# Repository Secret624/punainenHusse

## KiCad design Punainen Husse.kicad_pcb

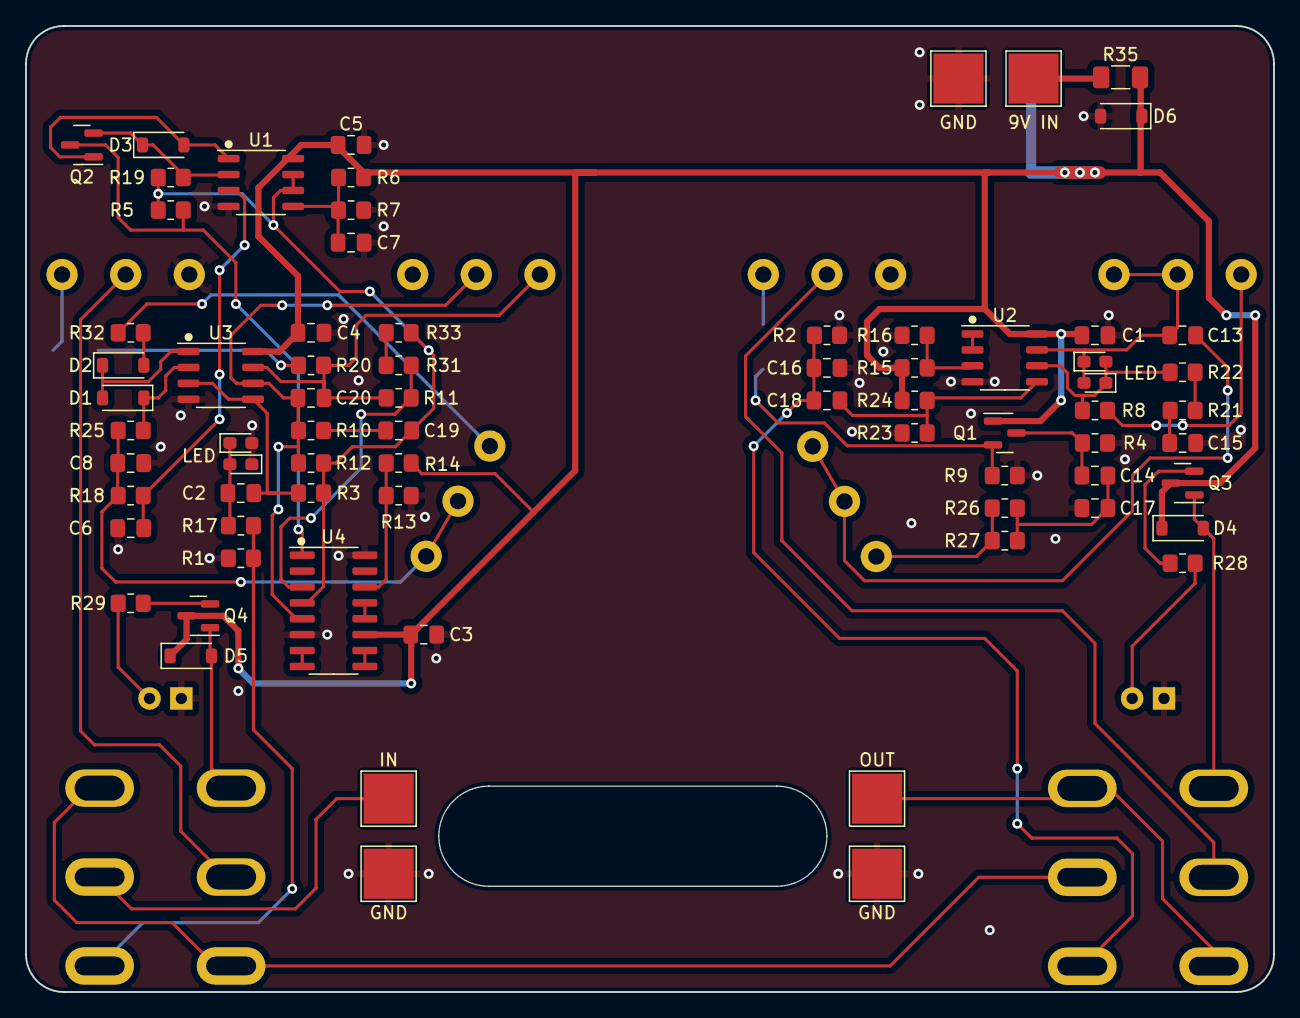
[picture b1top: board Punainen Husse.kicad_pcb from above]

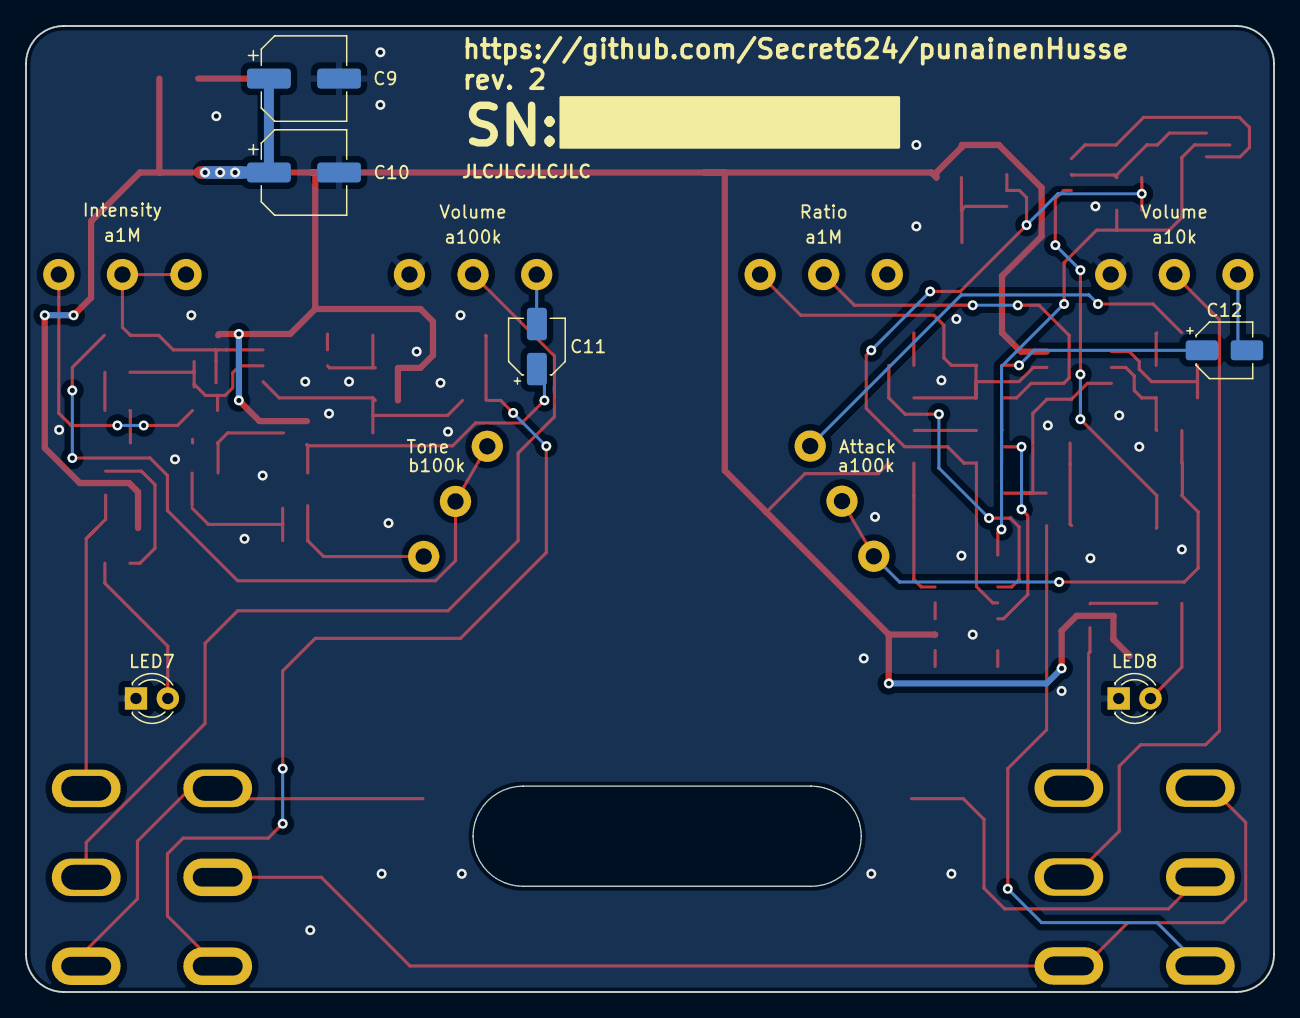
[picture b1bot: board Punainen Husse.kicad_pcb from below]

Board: 2 copper layers, 99.7 x 77.1 mm, 87 parts (14 on the bottom side), 54 nets.

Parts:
C1, C2, C3, C4, C5: 10nF; C_0805_2012Metric_Pad1.18x1.45mm_HandSolder
C6, C7, C8: 1uF; C_0805_2012Metric_Pad1.18x1.45mm_HandSolder
C9, C10: 100uF; CP_Elec_6.3x5.4
C11, C12: 10uF; CP_Elec_4x5.4
C13, C14: 100nF; C_0805_2012Metric_Pad1.18x1.45mm_HandSolder
C15: 220nF; C_0805_2012Metric_Pad1.18x1.45mm_HandSolder
C16: 1nF; C_0805_2012Metric_Pad1.18x1.45mm_HandSolder
C17: 3.3nF; C_0805_2012Metric_Pad1.18x1.45mm_HandSolder
C18: 47nF; C_0805_2012Metric_Pad1.18x1.45mm_HandSolder
C19: 4.7nF; C_0805_2012Metric_Pad1.18x1.45mm_HandSolder
C20: 100pF; C_0805_2012Metric_Pad1.18x1.45mm_HandSolder
D1, D2, D3, D4, D5: 1N4148W; D_SOD-123
D6: 1N4001; D_SOD-123
LED1, LED2, LED3, LED4: LED_Small; LED_0603_1608Metric_Pad1.05x0.95mm_HandSolder
LED7, LED8: LED_Small; LED_D3.0mm
Q1: MMBF4393LT1G; SOT-23
Q2: BC807; SOT-23
Q3, Q4: MMBF170; SOT-23
R1, R2, R3, R4, R5, R6, R7: 1M; R_0805_2012Metric_Pad1.20x1.40mm_HandSolder
R8, R9, R10, R11, R12, R13, R14, R15, R16: 10k; R_0805_2012Metric_Pad1.20x1.40mm_HandSolder
R17, R18, R19, R20, R21, R22: 1k; R_0805_2012Metric_Pad1.20x1.40mm_HandSolder
R23, R24, R25: 470k; R_0805_2012Metric_Pad1.20x1.40mm_HandSolder
R26, R27, R28, R29: 4.7k; R_0805_2012Metric_Pad1.20x1.40mm_HandSolder
R31, R32, R33: 100Ω; R_0805_2012Metric_Pad1.20x1.40mm_HandSolder
R35: 39Ω; R_1206_3216Metric_Pad1.30x1.75mm_HandSolder
Rv1, Rv5: a1M; UT right angle long pin
Rv2: b100k; UT right angle long pin
Rv3, Rv4: a100k; UT right angle long pin
Rv6: a10k; UT right angle long pin
SW1, SW2: SW_DPDT_x2; Ural dpdt
TP1: OUT; TestPoint_Pad_4.0x4.0mm
TP2: IN; TestPoint_Pad_4.0x4.0mm
TP3, TP4, TP11: GND; TestPoint_Pad_4.0x4.0mm
TP12: 9V IN; TestPoint_Pad_4.0x4.0mm
U1, U2, U3: TL072; SO-8_3.9x4.9mm_P1.27mm
U4: LM13700; SOP-16_3.9x9.9mm_P1.27mm

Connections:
9V in: R35.1, TP12.1
+5V: C19.2, R3.1, R5.1, R12.1, R19.1, R33.2, U1.6 (-), U1.7, U4.4 (-)
+9V: C1.1, C3.1, C4.1, C5.1, C9.1, C10.1, D4.1 (K), D5.1 (K), D6.1 (K), Q1.1 (D), Q3.3 (D), Q4.3 (D), R6.1, R14.1, R15.1, R24.1, R35.2, U1.8 (V+), U2.8 (V+), U3.8 (V+), U4.11 (V+)
FS_engi: D5.2 (A), Q4.1 (G), SW2.4 (A)
FS_red: D4.2 (A), Q3.1 (G), SW1.4 (A)
GND: C1.2, C3.2, C4.2, C5.2, C6.2, C7.1, C8.2, C9.2, C10.2, C15.2, C16.2, C17.2, D6.2 (A), LED3.1 (K), LED4.2 (A), LED7.1 (K), LED8.1 (K), R1.2, R2.2, R4.2, R7.2, R9.2, R13.2, R16.2, R23.2, Rv3.1, Rv6.1, TP3.1, TP4.1, TP11.1, U1.4 (V-), U2.4 (V-), U3.4 (V-), U4.6 (V-), U4.16
IN_engi: SW2.2 (B), TP2.1
IN_engi_pcb: R1.1, R17.1, SW2.1 (A)
IN_red: SW1.2 (B), SW2.3 (C), SW2.6 (C)
IN_red_pcb: C16.1, C18.1, R2.1, SW1.1 (A)
unnamed: C8.1, R18.1, R25.1, Rv4.2, Rv4.3
unnamed: C11.2, Rv3.3
unnamed: C12.1, R20.2
unnamed: C12.2, Rv6.3
unnamed: C13.1, Rv2.2, Rv2.3
unnamed: C14.2, C17.1, R26.1, R27.1
unnamed: C15.1, R21.2
unnamed: C19.1, R10.1
unnamed: C20.1, R11.2, R20.1, Rv5.1, U3.7
unnamed: D1.2 (A), D2.1 (K), U3.1
unnamed: D1.1 (K), R25.2, U3.2 (-)
unnamed: D2.2 (A), R32.1
unnamed: D3.2 (A), Q2.1 (B), U1.1
unnamed: D3.1 (K), Q2.2 (E), R19.2, U1.2 (-)
unnamed: C13.2, LED1.2 (A), LED2.1 (K), Rv1.2, Rv1.3, U2.7
unnamed: LED1.1 (K), LED2.2 (A), R8.2, R22.2, U2.6 (-)
unnamed: C2.2, LED3.2 (A), LED4.1 (K), R17.2
unnamed: LED7.2 (A), R28.2
unnamed: LED8.2 (A), R29.2
unnamed: C14.1, Q1.3 (G), R4.1
unnamed: C11.1, Q1.2 (S), R9.1
unnamed: Q2.3 (C), R5.2, U4.1
unnamed: Q3.2 (S), R28.1
unnamed: Q4.2 (S), R29.1
unnamed: R8.1, Rv1.1
unnamed: R21.1, R22.1
unnamed: R26.2, R27.2, Rv2.1
unnamed: R31.2, R33.1
unnamed: R32.2, Rv4.1
unnamed: C6.1, R18.2, U1.3 (+)
unnamed: C7.2, R6.2, R7.1, U1.5 (+)
unnamed: R15.2, R16.1, U2.3 (+)
unnamed: U2.1, U2.2 (-)
unnamed: C18.2, R23.1, R24.2, U2.5 (+)
unnamed: C2.1, R3.2, U3.3 (+), U3.5 (+)
unnamed: C20.2, R10.2, R12.2, Rv5.2, U3.6 (-), U4.5
unnamed: U4.7, U4.8
unnamed: U4.9, U4.10
unnamed: R13.1, R14.2, U4.14 (+)
unnamed: U4.12, U4.13 (-)
unnamed: R11.1, R31.1, U4.3 (+)
OUT_engi_pcb: Rv6.2, SW2.5 (B)
OUT_red: SW1.3 (C), SW1.6 (C), TP1.1
OUT_red_pcb: Rv3.2, SW1.5 (B)

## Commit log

2023-10-31 kuva lisätty
2023-11-02 small fixes
2023-11-02 even smaller fixes
2023-11-18 Added gerbers
2023-12-13 Rev 2
2023-12-21 Revision 2
